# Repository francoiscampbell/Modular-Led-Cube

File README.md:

# Modular LED Cube
## !!!This is a work in progress!!!
A PCB with 4x4 columns of LEDs that can be attached in a coplanar fashion with others to increase the size. Supports up to 16x16 modules with up to 64 rows each, making up to a 64x64x64 cube.

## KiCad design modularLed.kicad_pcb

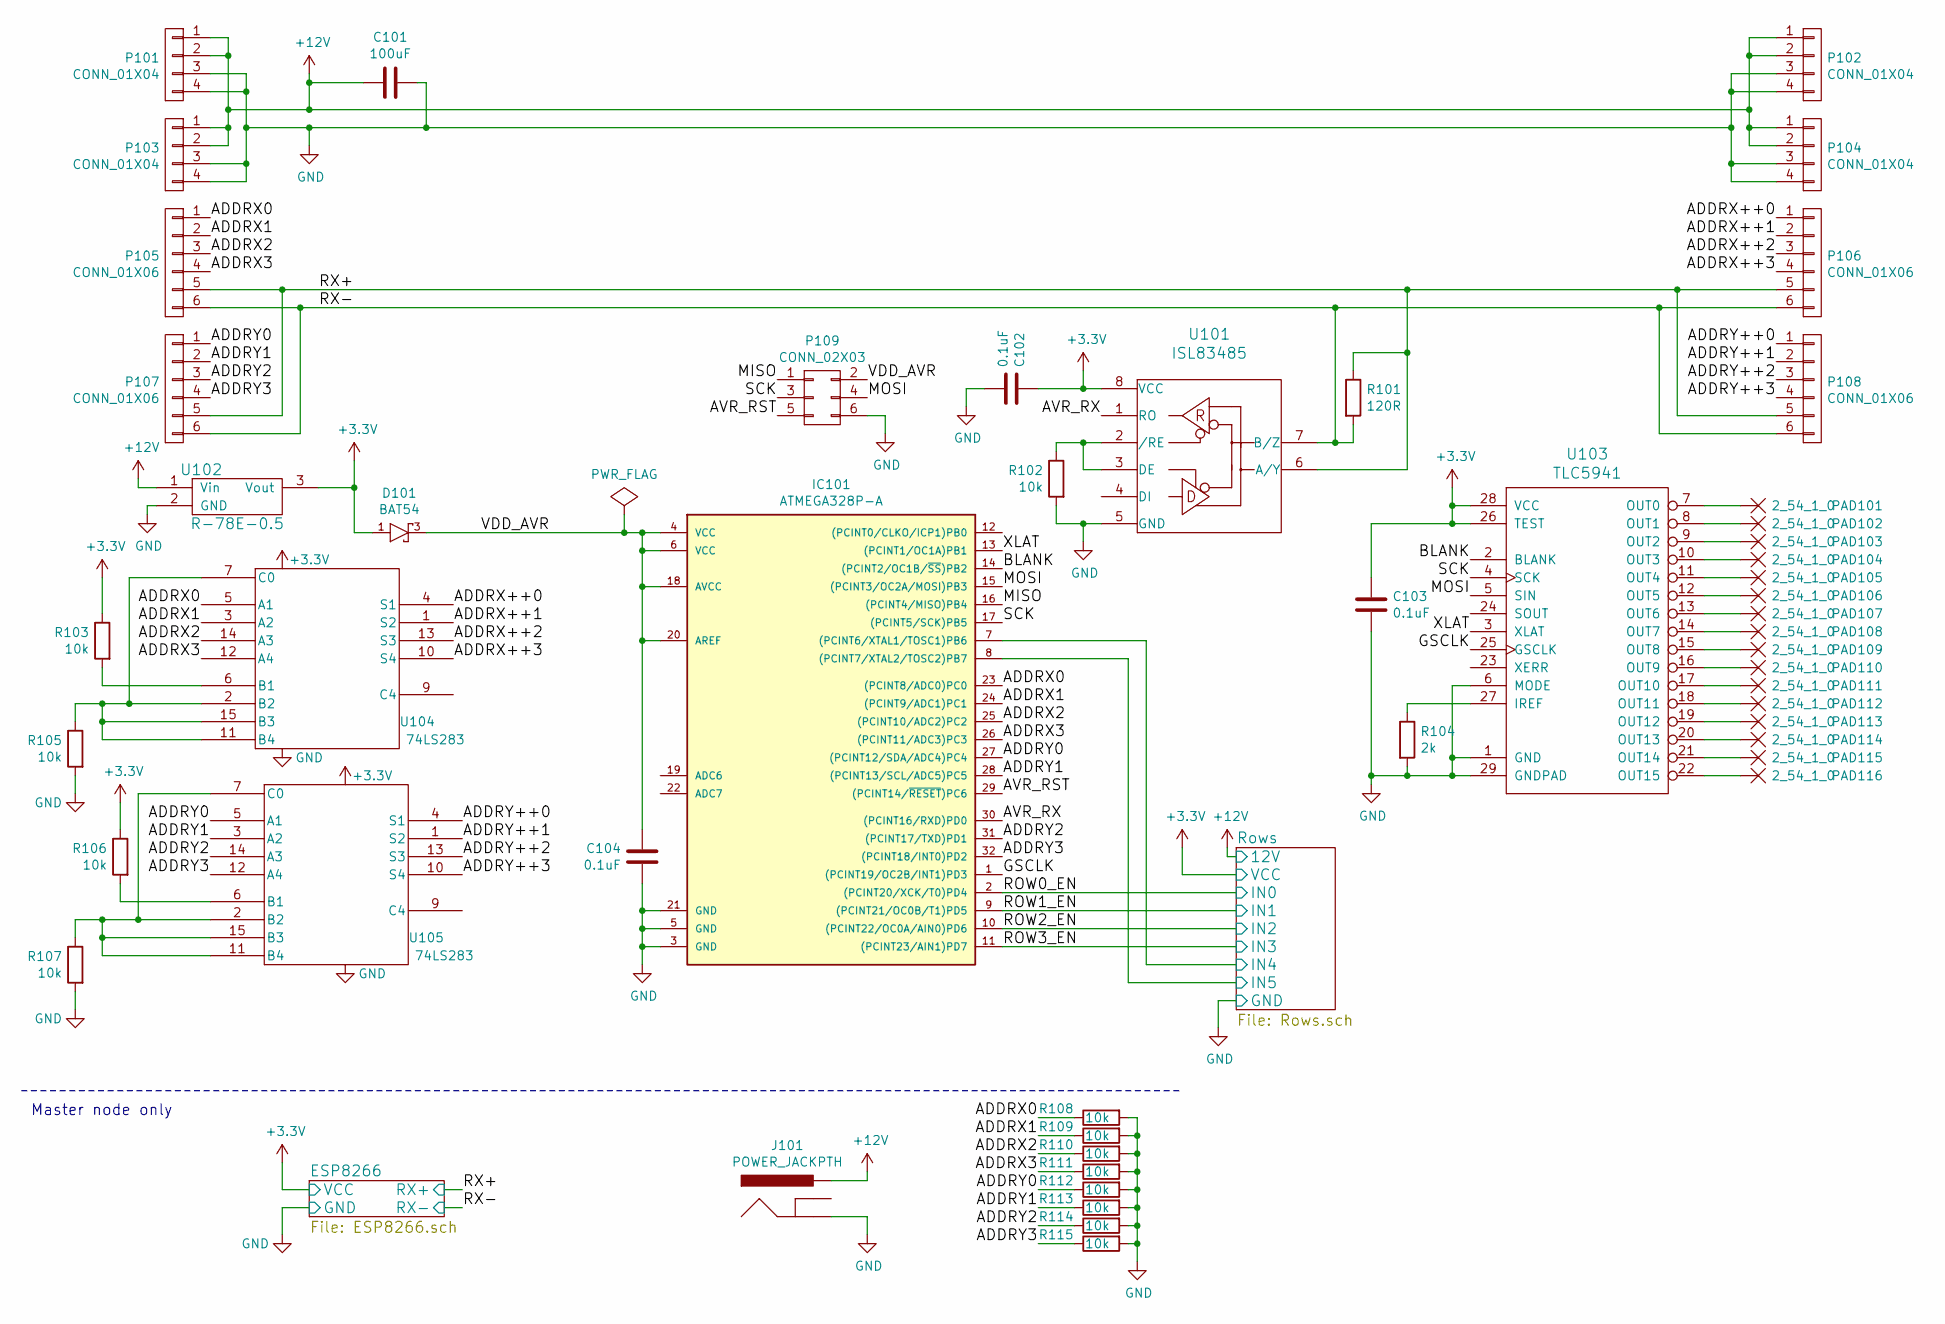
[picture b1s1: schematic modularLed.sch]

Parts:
C101: 100uF; c_elec_3x5.3
C102, C103, C104: 0.1uF; C_0603_HandSoldering
D101: BAT54; SOT-23
IC101: ATMEGA328P-A; TQFP-32_7x7mm_Pitch0.8mm
J101: POWER_JACKPTH; SparkFun-Connectors-POWER_JACK_PTH
P101, P103: CONN_01X04; Socket_Strip_Angled_1x04
P102, P104: CONN_01X04; Pin_Header_Angled_1x04
P105, P107: CONN_01X06; Socket_Strip_Angled_1x06
P106, P108: CONN_01X06; Pin_Header_Angled_1x06
P109: CONN_02X03; Pin_Header_Straight_2x03
PAD101, PAD102, PAD103, PAD104, PAD105, PAD106, PAD107, PAD108, PAD109, PAD110, PAD111, PAD112, PAD113, PAD114, PAD115, PAD116: 2_54_1_0; wirepad-2_54_1_0
R101: 120R; R_0603_HandSoldering
R102, R103, R105, R106, R107, R108, R109, R110, R111, R112, R113, R114, R115: 10k; R_0603_HandSoldering
R104: 2k; R_0603_HandSoldering
U101: ISL83485; SOIC-8_3.9x4.9mm_Pitch1.27mm
U102: R-78E-0.5
U103: TLC5941; MyLibrary-TSSOP28-GROUNDPAD
U104, U105: 74LS283; SOIC-16_3.9x9.9mm_Pitch1.27mm

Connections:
+3V3: C102.1, C103.1, D101.1 (A), R103.1, R106.1, U101.8 (VCC), U102.3 (Vout), U103.26 (TEST), U103.28 (VCC); also elsewhere on the board
+12V: C101.2, J101.PWR, P101.1, P101.2, P102.1, P102.2, P103.1, P103.2, P104.1, P104.2, U102.1 (Vin); also elsewhere on the board
/ADDRX0: IC101.23 ((PCINT8/ADC0)PC0), P105.1, R108.1, U104.5 (A1)
/ADDRX1: IC101.24 ((PCINT9/ADC1)PC1), P105.2, R109.1, U104.3 (A2)
/ADDRX2: IC101.25 ((PCINT10/ADC2)PC2), P105.3, R110.1, U104.14 (A3)
/ADDRX3: IC101.26 ((PCINT11/ADC3)PC3), P105.4, R111.1, U104.12 (A4)
/ADDRX++0: P106.1, U104.4 (S1)
/ADDRX++1: P106.2, U104.1 (S2)
/ADDRX++2: P106.3, U104.13 (S3)
/ADDRX++3: P106.4, U104.10 (S4)
/ADDRY0: IC101.27 ((PCINT12/SDA/ADC4)PC4), P107.1, R112.1, U105.5 (A1)
/ADDRY1: IC101.28 ((PCINT13/SCL/ADC5)PC5), P107.2, R113.1, U105.3 (A2)
/ADDRY2: IC101.31 ((PCINT17/TXD)PD1), P107.3, R114.1, U105.14 (A3)
/ADDRY3: IC101.32 ((PCINT18/INT0)PD2), P107.4, R115.1, U105.12 (A4)
/ADDRY++0: P108.1, U105.4 (S1)
/ADDRY++1: P108.2, U105.1 (S2)
/ADDRY++2: P108.3, U105.13 (S3)
/ADDRY++3: P108.4, U105.10 (S4)
/AVR_RST: IC101.29 ((PCINT14/~RESET~)PC6), P109.5
/AVR_RX: IC101.30 ((PCINT16/RXD)PD0), U101.1 (RO)
/BLANK: IC101.14 ((PCINT2/OC1B/~SS~)PB2), U103.2 (BLANK)
/GSCLK: IC101.1 ((PCINT19/OC2B/INT1)PD3), U103.25 (GSCLK)
/MISO: IC101.16 ((PCINT4/MISO)PB4), P109.1
/MOSI: IC101.15 ((PCINT3/OC2A/MOSI)PB3), P109.4, U103.5 (SIN)
/ROW0_EN: IC101.2 ((PCINT20/XCK/T0)PD4); also elsewhere on the board
/ROW1_EN: IC101.9 ((PCINT21/OC0B/T1)PD5); also elsewhere on the board
/ROW2_EN: IC101.10 ((PCINT22/OC0A/AIN0)PD6); also elsewhere on the board
/ROW3_EN: IC101.11 ((PCINT23/AIN1)PD7); also elsewhere on the board
/RX+: P105.5, P106.5, P107.5, P108.5, R101.1, U101.6 (A/Y); also elsewhere on the board
/RX-: P105.6, P106.6, P107.6, P108.6, R101.2, U101.7 (B/Z); also elsewhere on the board
/Rows/IN4: IC101.7 ((PCINT6/XTAL1/TOSC1)PB6); also elsewhere on the board
/Rows/IN5: IC101.8 ((PCINT7/XTAL2/TOSC2)PB7); also elsewhere on the board
/SCK: IC101.17 ((PCINT5/SCK)PB5), P109.3, U103.4 (SCK)
/VDD_AVR: C104.1, D101.3 (C), IC101.4 (VCC), IC101.6 (VCC), IC101.18 (AVCC), IC101.20 (AREF), P109.2
/XLAT: IC101.13 ((PCINT1/OC1A)PB1), U103.3 (XLAT)
GND: C101.1, C102.2, C103.2, C104.2, IC101.3 (GND), IC101.5 (GND), IC101.21 (GND), J101.GND, P101.3, P101.4, P102.3, P102.4, P103.3, P103.4, P104.3, P104.4, P109.6, R102.2, R104.2, R105.2, R107.2, R108.2, R109.2, R110.2, R111.2, R112.2, R113.2, R114.2, R115.2, U101.5 (GND), U102.2 (GND), U103.1 (GND), U103.6 (MODE), U103.29 (GNDPAD), U104.8 (GND), U105.8 (GND); also elsewhere on the board
unnamed: PAD101.1, U103.7 (OUT0)
unnamed: PAD102.1, U103.8 (OUT1)
unnamed: PAD103.1, U103.9 (OUT2)
unnamed: PAD104.1, U103.10 (OUT3)
unnamed: PAD105.1, U103.11 (OUT4)
unnamed: PAD106.1, U103.12 (OUT5)
unnamed: PAD107.1, U103.13 (OUT6)
unnamed: PAD108.1, U103.14 (OUT7)
unnamed: PAD109.1, U103.15 (OUT8)
unnamed: PAD110.1, U103.16 (OUT9)
unnamed: PAD111.1, U103.17 (OUT10)
unnamed: PAD112.1, U103.18 (OUT11)
unnamed: PAD113.1, U103.19 (OUT12)
unnamed: PAD114.1, U103.20 (OUT13)
unnamed: PAD115.1, U103.21 (OUT14)
unnamed: PAD116.1, U103.22 (OUT15)
unnamed: R102.1, U101.2 (/RE), U101.3 (DE)
unnamed: R103.2, U104.6 (B1)
unnamed: R104.1, U103.27 (IREF)
unnamed: R105.1, U104.2 (B2), U104.7 (C0), U104.11 (B4), U104.15 (B3)
unnamed: R106.2, U105.6 (B1)
unnamed: R107.1, U105.2 (B2), U105.7 (C0), U105.11 (B4), U105.15 (B3)
VCC: U104.16 (VCC), U105.16 (VCC)

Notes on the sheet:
Master node only

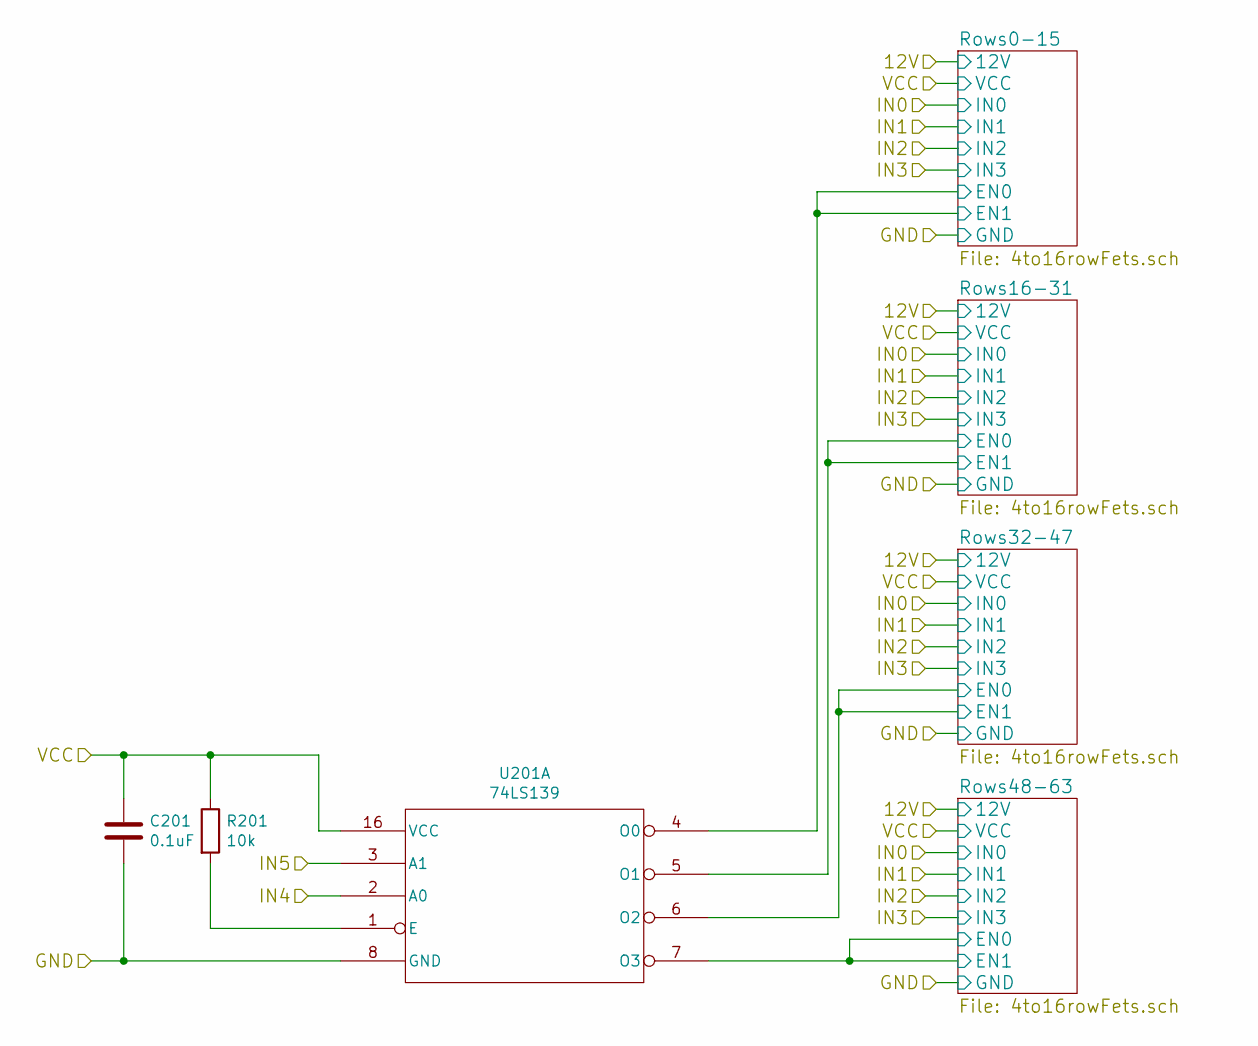
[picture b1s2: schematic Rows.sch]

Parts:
C201: 0.1uF; C_0603_HandSoldering
R201: 10k; R_0603_HandSoldering
U201: 74LS139; SOIC-16_3.9x9.9mm_Pitch1.27mm

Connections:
+3V3: C201.1, R201.1, U201.16 (VCC); also elsewhere on the board
/Rows/IN4: U201.2 (A0); also elsewhere on the board
/Rows/IN5: U201.3 (A1); also elsewhere on the board
/Rows/Rows0-15/EN0: U201.4 (O0); also elsewhere on the board
/Rows/Rows16-31/EN0: U201.5 (O1); also elsewhere on the board
/Rows/Rows32-47/EN0: U201.6 (O2); also elsewhere on the board
/Rows/Rows48-63/EN0: U201.7 (O3); also elsewhere on the board
GND: C201.2, U201.8 (GND); also elsewhere on the board
unnamed: R201.2, U201.1 (E)

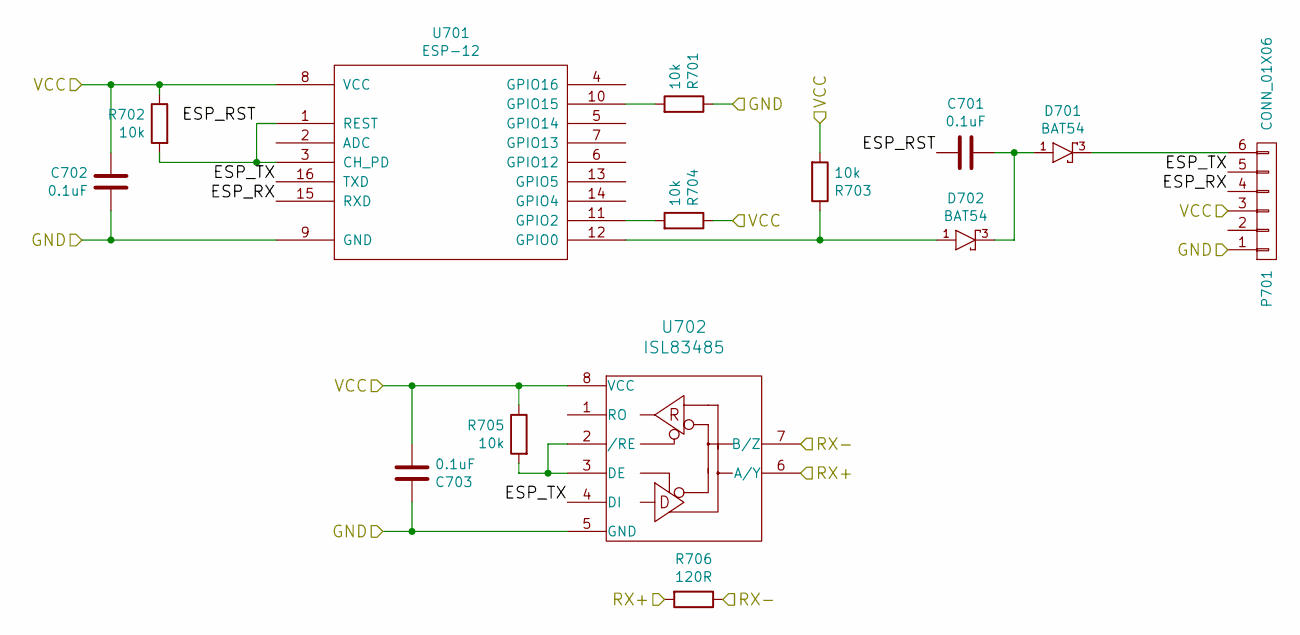
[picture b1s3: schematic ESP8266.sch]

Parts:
C701, C702, C703: 0.1uF; C_0603_HandSoldering
D701, D702: BAT54; SOT-23
P701: CONN_01X06; Pin_Header_Angled_1x06
R701, R702, R703, R704, R705: 10k; R_0603_HandSoldering
R706: 120R; R_0603_HandSoldering
U701: ESP-12
U702: ISL83485; SOIC-8_3.9x4.9mm_Pitch1.27mm

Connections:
+3V3: C702.1, C703.2, P701.3, R702.1, R703.2, R704.1, R705.1, U701.8 (VCC), U702.8 (VCC); also elsewhere on the board
/ESP8266/ESP_RST: C701.2, R702.2, U701.1 (REST), U701.3 (CH_PD)
/ESP8266/ESP_RX: P701.4, U701.15 (RXD)
/ESP8266/ESP_TX: P701.5, U701.16 (TXD), U702.4 (DI)
/RX+: R706.2, U702.6 (A/Y); also elsewhere on the board
/RX-: R706.1, U702.7 (B/Z); also elsewhere on the board
GND: C702.2, C703.1, P701.1, R701.1, U701.9 (GND), U702.5 (GND); also elsewhere on the board
unnamed: C701.1, D701.1 (A), D702.3 (C)
unnamed: D701.3 (C), P701.6
unnamed: D702.1 (A), R703.1, U701.12 (GPIO0)
unnamed: R701.2, U701.10 (GPIO15)
unnamed: R704.2, U701.11 (GPIO2)
unnamed: R705.2, U702.2 (/RE), U702.3 (DE)

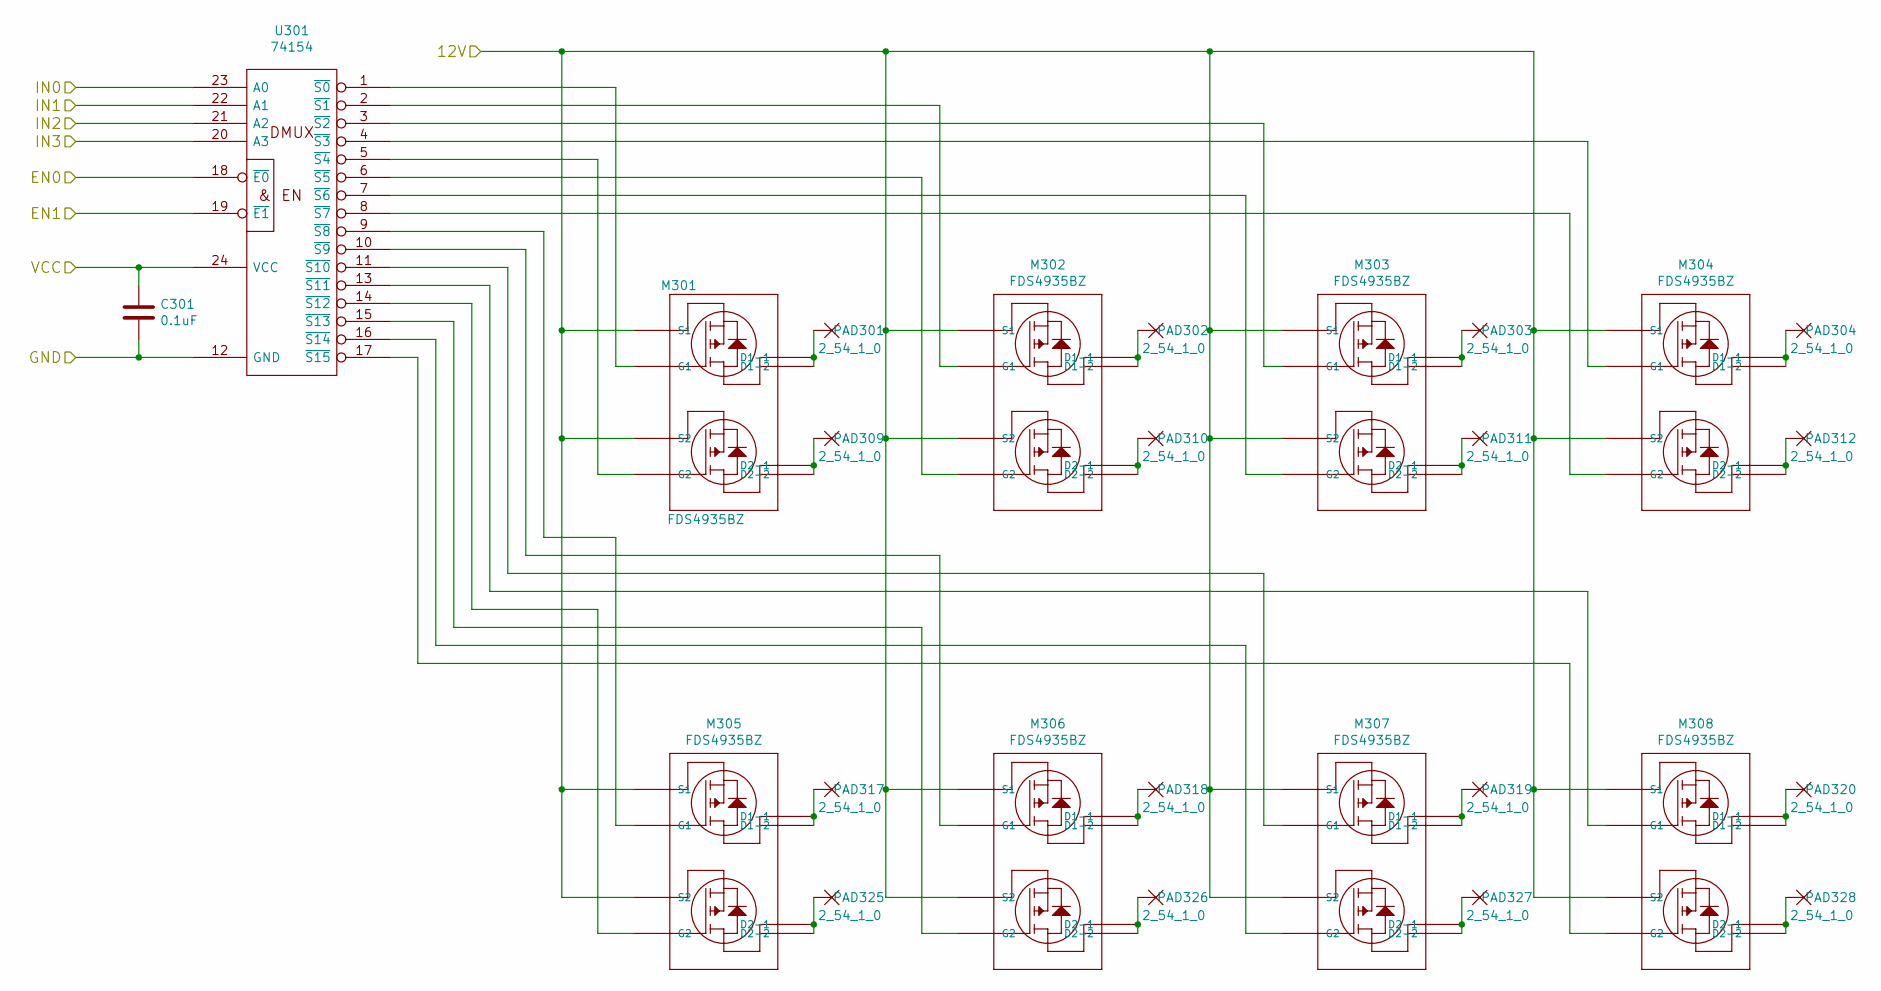
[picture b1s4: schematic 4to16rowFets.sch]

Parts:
C301: 0.1uF; C_0603_HandSoldering
M301, M302, M303, M304, M305, M306, M307, M308: FDS4935BZ; SOIC-8_3.9x4.9mm_Pitch1.27mm
PAD301, PAD302, PAD303, PAD304, PAD309, PAD310, PAD311, PAD312, PAD317, PAD318, PAD319, PAD320, PAD325, PAD326, PAD327, PAD328: 2_54_1_0; wirepad-2_54_1_0
U301: 74154; SOIC-24_7.5x15.4mm_Pitch1.27mm

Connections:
+3V3: C301.1, U301.24 (VCC); also elsewhere on the board
+12V: M301.1 (S2), M301.3 (S1), M302.1 (S2), M302.3 (S1), M303.1 (S2), M303.3 (S1), M304.1 (S2), M304.3 (S1), M305.1 (S2), M305.3 (S1), M306.1 (S2), M306.3 (S1), M307.1 (S2), M307.3 (S1), M308.1 (S2), M308.3 (S1); also elsewhere on the board
/ROW0_EN: U301.23 (A0); also elsewhere on the board
/ROW1_EN: U301.22 (A1); also elsewhere on the board
/ROW2_EN: U301.21 (A2); also elsewhere on the board
/ROW3_EN: U301.20 (A3); also elsewhere on the board
/Rows/Rows0-15/EN0: U301.18 (~E0), U301.19 (~E1); also elsewhere on the board
GND: C301.2, U301.12 (GND); also elsewhere on the board
unnamed: M301.2 (G2), U301.5 (~S4)
unnamed: M301.4 (G1), U301.1 (~S0)
unnamed: M301.5 (D1-1), M301.6 (D1-2), PAD301.1
unnamed: M301.7 (D2-1), M301.8 (D2-2), PAD309.1
unnamed: M302.2 (G2), U301.6 (~S5)
unnamed: M302.4 (G1), U301.2 (~S1)
unnamed: M302.5 (D1-1), M302.6 (D1-2), PAD302.1
unnamed: M302.7 (D2-1), M302.8 (D2-2), PAD310.1
unnamed: M303.2 (G2), U301.7 (~S6)
unnamed: M303.4 (G1), U301.3 (~S2)
unnamed: M303.5 (D1-1), M303.6 (D1-2), PAD303.1
unnamed: M303.7 (D2-1), M303.8 (D2-2), PAD311.1
unnamed: M304.2 (G2), U301.8 (~S7)
unnamed: M304.4 (G1), U301.4 (~S3)
unnamed: M304.5 (D1-1), M304.6 (D1-2), PAD304.1
unnamed: M304.7 (D2-1), M304.8 (D2-2), PAD312.1
unnamed: M305.2 (G2), U301.14 (~S12)
unnamed: M305.4 (G1), U301.9 (~S8)
unnamed: M305.5 (D1-1), M305.6 (D1-2), PAD317.1
unnamed: M305.7 (D2-1), M305.8 (D2-2), PAD325.1
unnamed: M306.2 (G2), U301.15 (~S13)
unnamed: M306.4 (G1), U301.10 (~S9)
unnamed: M306.5 (D1-1), M306.6 (D1-2), PAD318.1
unnamed: M306.7 (D2-1), M306.8 (D2-2), PAD326.1
unnamed: M307.2 (G2), U301.16 (~S14)
unnamed: M307.4 (G1), U301.11 (~S10)
unnamed: M307.5 (D1-1), M307.6 (D1-2), PAD319.1
unnamed: M307.7 (D2-1), M307.8 (D2-2), PAD327.1
unnamed: M308.2 (G2), U301.17 (~S15)
unnamed: M308.4 (G1), U301.13 (~S11)
unnamed: M308.5 (D1-1), M308.6 (D1-2), PAD320.1
unnamed: M308.7 (D2-1), M308.8 (D2-2), PAD328.1

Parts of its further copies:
C401, C501, C601: 0.1uF; C_0603_HandSoldering
M401, M402, M403, M404, M405, M406, M407, M408, M501, M502, M503, M504, M505, M506, M507, M508, M601, M602, M603, M604, M605, M606, M607, M608: FDS4935BZ; SOIC-8_3.9x4.9mm_Pitch1.27mm
PAD401, PAD402, PAD403, PAD404, PAD409, PAD410, PAD411, PAD412, PAD417, PAD418, PAD419, PAD420, PAD425, PAD426, PAD427, PAD428, PAD501, PAD502, PAD503, PAD504, PAD509, PAD510, PAD511, PAD512, PAD517, PAD518, PAD519, PAD520, PAD525, PAD526, PAD527, PAD528, PAD601, PAD602, PAD603, PAD604, PAD609, PAD610, PAD611, PAD612, PAD617, PAD618, PAD619, PAD620, PAD625, PAD626, PAD627, PAD628: 2_54_1_0; wirepad-2_54_1_0
U401, U501, U601: 74154; SOIC-24_7.5x15.4mm_Pitch1.27mm

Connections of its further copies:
+3V3: C401.1, C501.1, C601.1, U401.24 (VCC), U501.24 (VCC), U601.24 (VCC); also elsewhere on the board
+12V: M401.1 (S2), M401.3 (S1), M402.1 (S2), M402.3 (S1), M403.1 (S2), M403.3 (S1), M404.1 (S2), M404.3 (S1), M405.1 (S2), M405.3 (S1), M406.1 (S2), M406.3 (S1), M407.1 (S2), M407.3 (S1), M408.1 (S2), M408.3 (S1), M501.1 (S2), M501.3 (S1), M502.1 (S2), M502.3 (S1), M503.1 (S2), M503.3 (S1), M504.1 (S2), M504.3 (S1), M505.1 (S2), M505.3 (S1), M506.1 (S2), M506.3 (S1), M507.1 (S2), M507.3 (S1), M508.1 (S2), M508.3 (S1), M601.1 (S2), M601.3 (S1), M602.1 (S2), M602.3 (S1), M603.1 (S2), M603.3 (S1), M604.1 (S2), M604.3 (S1), M605.1 (S2), M605.3 (S1), M606.1 (S2), M606.3 (S1), M607.1 (S2), M607.3 (S1), M608.1 (S2), M608.3 (S1); also elsewhere on the board
/ROW0_EN: U401.23 (A0), U501.23 (A0), U601.23 (A0); also elsewhere on the board
/ROW1_EN: U401.22 (A1), U501.22 (A1), U601.22 (A1); also elsewhere on the board
/ROW2_EN: U401.21 (A2), U501.21 (A2), U601.21 (A2); also elsewhere on the board
/ROW3_EN: U401.20 (A3), U501.20 (A3), U601.20 (A3); also elsewhere on the board
/Rows/Rows16-31/EN0: U601.18 (~E0), U601.19 (~E1); also elsewhere on the board
/Rows/Rows32-47/EN0: U401.18 (~E0), U401.19 (~E1); also elsewhere on the board
/Rows/Rows48-63/EN0: U501.18 (~E0), U501.19 (~E1); also elsewhere on the board
GND: C401.2, C501.2, C601.2, U401.12 (GND), U501.12 (GND), U601.12 (GND); also elsewhere on the board
unnamed: M401.2 (G2), U401.5 (~S4)
unnamed: M401.4 (G1), U401.1 (~S0)
unnamed: M401.5 (D1-1), M401.6 (D1-2), PAD401.1
unnamed: M401.7 (D2-1), M401.8 (D2-2), PAD409.1
unnamed: M402.2 (G2), U401.6 (~S5)
unnamed: M402.4 (G1), U401.2 (~S1)
unnamed: M402.5 (D1-1), M402.6 (D1-2), PAD402.1
unnamed: M402.7 (D2-1), M402.8 (D2-2), PAD410.1
unnamed: M403.2 (G2), U401.7 (~S6)
unnamed: M403.4 (G1), U401.3 (~S2)
unnamed: M403.5 (D1-1), M403.6 (D1-2), PAD403.1
unnamed: M403.7 (D2-1), M403.8 (D2-2), PAD411.1
unnamed: M404.2 (G2), U401.8 (~S7)
unnamed: M404.4 (G1), U401.4 (~S3)
unnamed: M404.5 (D1-1), M404.6 (D1-2), PAD404.1
unnamed: M404.7 (D2-1), M404.8 (D2-2), PAD412.1
unnamed: M405.2 (G2), U401.14 (~S12)
unnamed: M405.4 (G1), U401.9 (~S8)
unnamed: M405.5 (D1-1), M405.6 (D1-2), PAD417.1
unnamed: M405.7 (D2-1), M405.8 (D2-2), PAD425.1
unnamed: M406.2 (G2), U401.15 (~S13)
unnamed: M406.4 (G1), U401.10 (~S9)
unnamed: M406.5 (D1-1), M406.6 (D1-2), PAD418.1
unnamed: M406.7 (D2-1), M406.8 (D2-2), PAD426.1
unnamed: M407.2 (G2), U401.16 (~S14)
unnamed: M407.4 (G1), U401.11 (~S10)
unnamed: M407.5 (D1-1), M407.6 (D1-2), PAD419.1
unnamed: M407.7 (D2-1), M407.8 (D2-2), PAD427.1
unnamed: M408.2 (G2), U401.17 (~S15)
unnamed: M408.4 (G1), U401.13 (~S11)
unnamed: M408.5 (D1-1), M408.6 (D1-2), PAD420.1
unnamed: M408.7 (D2-1), M408.8 (D2-2), PAD428.1
unnamed: M501.2 (G2), U501.5 (~S4)
unnamed: M501.4 (G1), U501.1 (~S0)
unnamed: M501.5 (D1-1), M501.6 (D1-2), PAD501.1
unnamed: M501.7 (D2-1), M501.8 (D2-2), PAD509.1
unnamed: M502.2 (G2), U501.6 (~S5)
unnamed: M502.4 (G1), U501.2 (~S1)
unnamed: M502.5 (D1-1), M502.6 (D1-2), PAD502.1
unnamed: M502.7 (D2-1), M502.8 (D2-2), PAD510.1
unnamed: M503.2 (G2), U501.7 (~S6)
unnamed: M503.4 (G1), U501.3 (~S2)
unnamed: M503.5 (D1-1), M503.6 (D1-2), PAD503.1
unnamed: M503.7 (D2-1), M503.8 (D2-2), PAD511.1
unnamed: M504.2 (G2), U501.8 (~S7)
unnamed: M504.4 (G1), U501.4 (~S3)
unnamed: M504.5 (D1-1), M504.6 (D1-2), PAD504.1
unnamed: M504.7 (D2-1), M504.8 (D2-2), PAD512.1
unnamed: M505.2 (G2), U501.14 (~S12)
unnamed: M505.4 (G1), U501.9 (~S8)
unnamed: M505.5 (D1-1), M505.6 (D1-2), PAD517.1
unnamed: M505.7 (D2-1), M505.8 (D2-2), PAD525.1
unnamed: M506.2 (G2), U501.15 (~S13)
unnamed: M506.4 (G1), U501.10 (~S9)
unnamed: M506.5 (D1-1), M506.6 (D1-2), PAD518.1
unnamed: M506.7 (D2-1), M506.8 (D2-2), PAD526.1
unnamed: M507.2 (G2), U501.16 (~S14)
unnamed: M507.4 (G1), U501.11 (~S10)
unnamed: M507.5 (D1-1), M507.6 (D1-2), PAD519.1
unnamed: M507.7 (D2-1), M507.8 (D2-2), PAD527.1
unnamed: M508.2 (G2), U501.17 (~S15)
unnamed: M508.4 (G1), U501.13 (~S11)
unnamed: M508.5 (D1-1), M508.6 (D1-2), PAD520.1
unnamed: M508.7 (D2-1), M508.8 (D2-2), PAD528.1
unnamed: M601.2 (G2), U601.5 (~S4)
unnamed: M601.4 (G1), U601.1 (~S0)
unnamed: M601.5 (D1-1), M601.6 (D1-2), PAD601.1
unnamed: M601.7 (D2-1), M601.8 (D2-2), PAD609.1
unnamed: M602.2 (G2), U601.6 (~S5)
unnamed: M602.4 (G1), U601.2 (~S1)
unnamed: M602.5 (D1-1), M602.6 (D1-2), PAD602.1
unnamed: M602.7 (D2-1), M602.8 (D2-2), PAD610.1
unnamed: M603.2 (G2), U601.7 (~S6)
unnamed: M603.4 (G1), U601.3 (~S2)
unnamed: M603.5 (D1-1), M603.6 (D1-2), PAD603.1
unnamed: M603.7 (D2-1), M603.8 (D2-2), PAD611.1
unnamed: M604.2 (G2), U601.8 (~S7)
unnamed: M604.4 (G1), U601.4 (~S3)
unnamed: M604.5 (D1-1), M604.6 (D1-2), PAD604.1
unnamed: M604.7 (D2-1), M604.8 (D2-2), PAD612.1
unnamed: M605.2 (G2), U601.14 (~S12)
unnamed: M605.4 (G1), U601.9 (~S8)
unnamed: M605.5 (D1-1), M605.6 (D1-2), PAD617.1
unnamed: M605.7 (D2-1), M605.8 (D2-2), PAD625.1
unnamed: M606.2 (G2), U601.15 (~S13)
unnamed: M606.4 (G1), U601.10 (~S9)
unnamed: M606.5 (D1-1), M606.6 (D1-2), PAD618.1
unnamed: M606.7 (D2-1), M606.8 (D2-2), PAD626.1
unnamed: M607.2 (G2), U601.16 (~S14)
unnamed: M607.4 (G1), U601.11 (~S10)
unnamed: M607.5 (D1-1), M607.6 (D1-2), PAD619.1
unnamed: M607.7 (D2-1), M607.8 (D2-2), PAD627.1
unnamed: M608.2 (G2), U601.17 (~S15)
unnamed: M608.4 (G1), U601.13 (~S11)
unnamed: M608.5 (D1-1), M608.6 (D1-2), PAD620.1
unnamed: M608.7 (D2-1), M608.8 (D2-2), PAD628.1

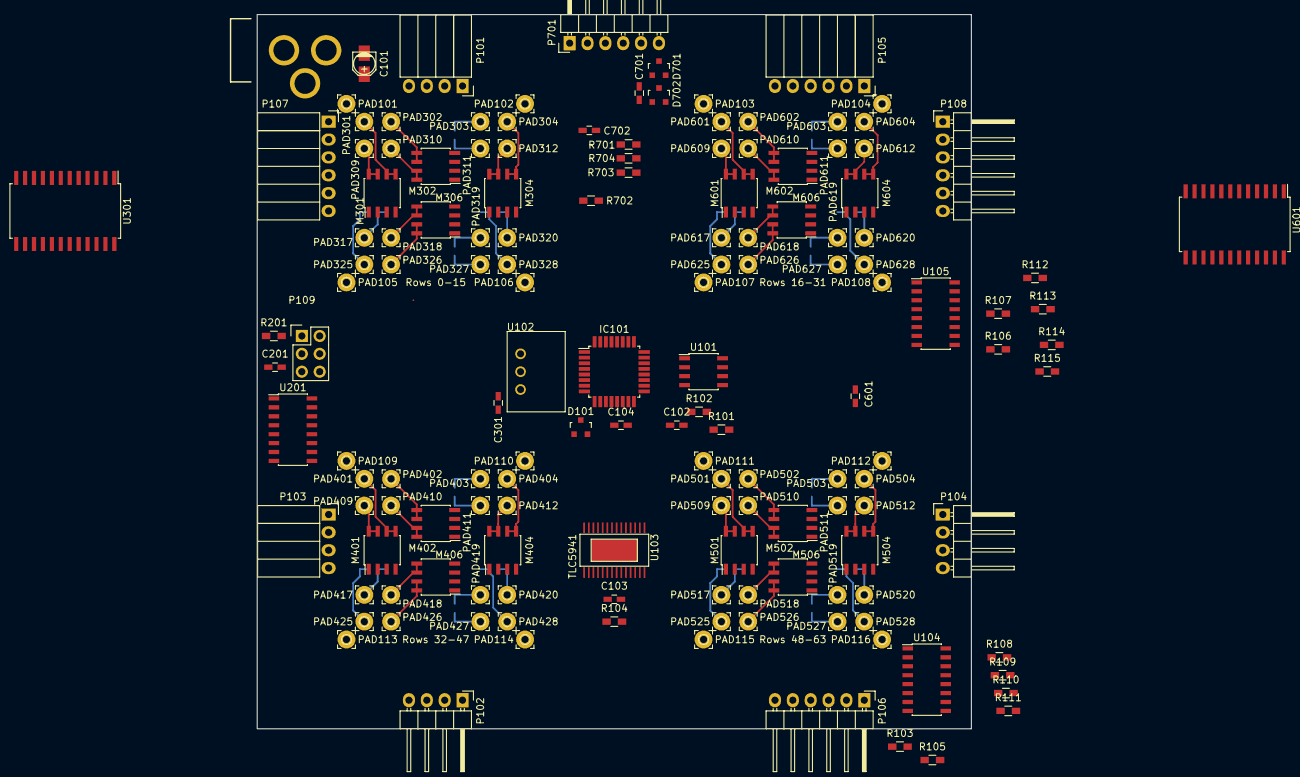
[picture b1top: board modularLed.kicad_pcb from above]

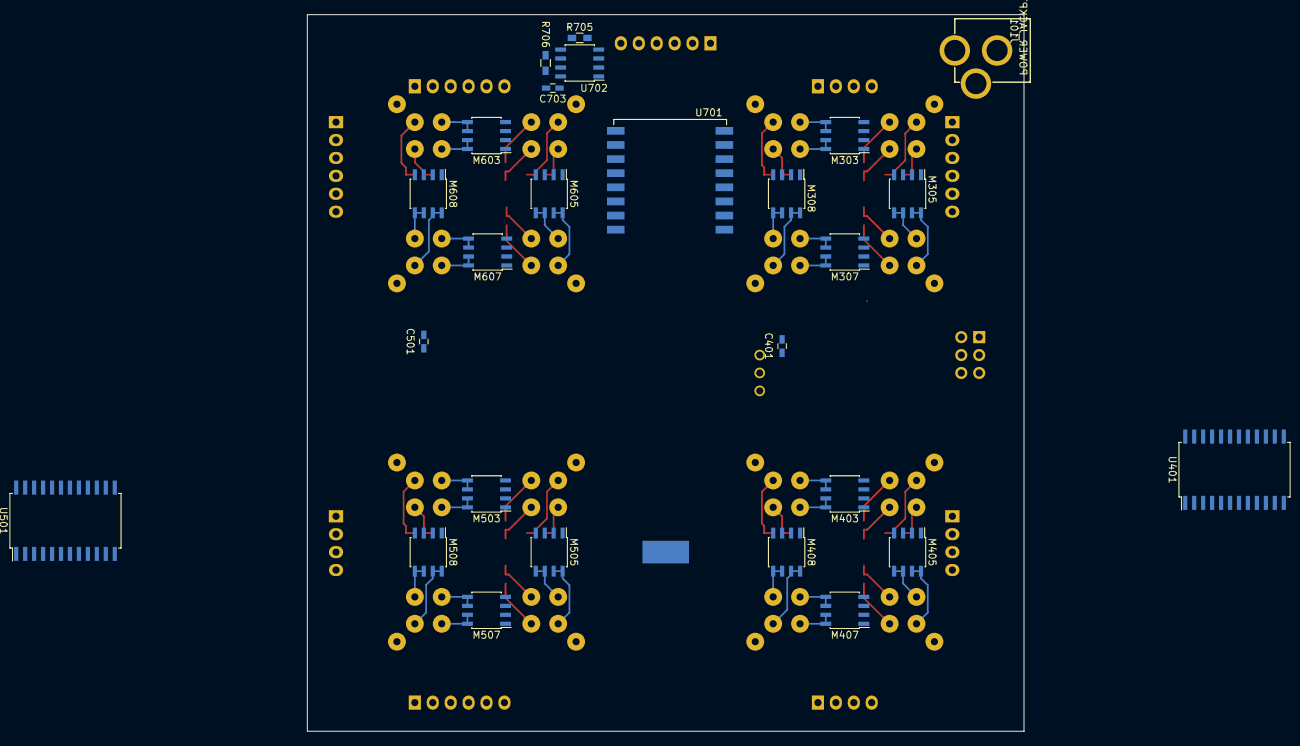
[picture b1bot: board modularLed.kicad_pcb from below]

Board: 2 copper layers, 101.6 x 101.6 mm, 173 parts (25 on the bottom side), 201 nets.

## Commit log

2016-04-20 Initial commit. Sch complete, PCB ready for placement
2016-04-20 Basic README
2016-04-20 Typo in README
2016-04-20 First quadrant of rows
2016-04-20 Second quadrant of rows
2016-04-20 Third quadrant of rows
2016-04-20 Fourth quadrant of rows
2016-04-20 First quadrant of fets placed
2016-04-20 Second and third quadrant of fets placed
2016-04-20 Rough component placement
2016-04-20 Improved connector placement
2016-04-20 Routed fet to row signals
